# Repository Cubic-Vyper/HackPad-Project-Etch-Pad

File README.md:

# HackPad-Project-Etch-Pad
This is my repository for my Hackpad called "Etch-Pad".
This HackPad has two layers. In the first, the rotary encoders control the mouse like an Etch-n-Sketch, and the switchs have some useful macros. On the second layer the rotary encoders control volume and led brightness, and the switches have some useful macros.

Blueprint Page:https://blueprint.hackclub.com/projects/10732

Buttons:
Layer 0: Screenshot, Paste, Parrot, Space

Layer 1: Previous track, Play/Pause+RickRoll, Next track, Spam E

Encoders:
Layer 0: Mouse control

Layer 1: Volume control + Led brightness

Parts Used:

Seeed XIAO RP2040

4x MX-Style switches

2x EC11 Rotary encoders

4x white blank DSA keycaps

4x SK6812 MINI-E LEDs

4x M3x16mm screws

4x M3x5mx4mm heatset inserts

____________________________________________________________________________________________________

This is the assembled model of my hackpad and what it should look like:

Schematic Screenshot:

PCB Screenshot:

to assemble the case, first collect all of your parts:

next insert the assembled PCB into the bottem half of the case:

then place the top plate on and screw it together:

finnaly attach the keycaps and the enchoder knobs:

plug it up:

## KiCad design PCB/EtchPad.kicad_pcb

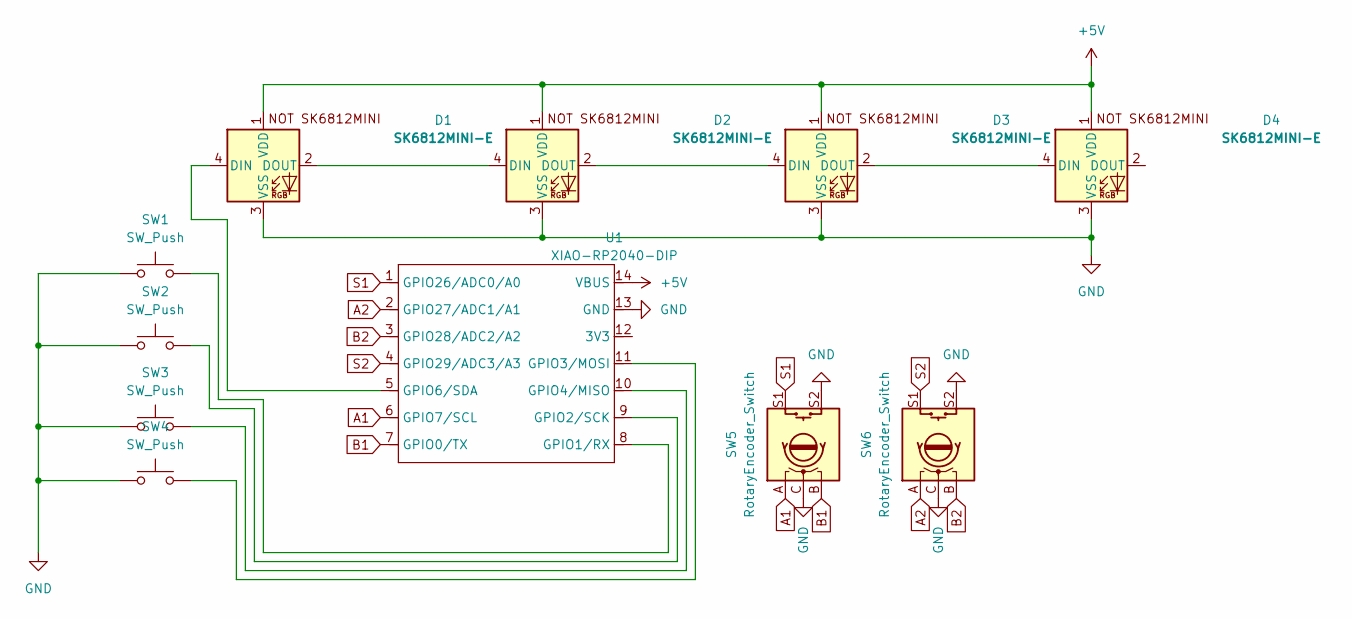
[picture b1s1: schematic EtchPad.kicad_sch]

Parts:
D1, D2, D3, D4: SK6812MINI-E; SK6812MINI-E_fixed
SW1, SW2, SW3, SW4: SW_Push; SW_Cherry_MX_1.00u_PCB
SW5, SW6: RotaryEncoder_Switch; RotaryEncoder_Alps_EC11E-Switch_Vertical_H20mm
U1: XIAO-RP2040-DIP

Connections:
+5V: D1.1 (VDD), D2.1 (VDD), D3.1 (VDD), D4.1 (VDD), U1.14 (VBUS)
A1: SW5.A, U1.6 (GPIO7/SCL)
A2: SW6.A, U1.2 (GPIO27/ADC1/A1)
B1: SW5.B, U1.7 (GPIO0/TX)
B2: SW6.B, U1.3 (GPIO28/ADC2/A2)
GND: D1.3 (VSS), D2.3 (VSS), D3.3 (VSS), D4.3 (VSS), SW1.1, SW2.1, SW3.1, SW4.1, SW5.C, SW5.S2, SW6.C, SW6.S2, U1.13 (GND)
unnamed: D1.4 (DIN), U1.5 (GPIO6/SDA)
unnamed: D1.2 (DOUT), D2.4 (DIN)
unnamed: D2.2 (DOUT), D3.4 (DIN)
unnamed: D3.2 (DOUT), D4.4 (DIN)
unnamed: SW1.2, U1.8 (GPIO1/RX)
unnamed: SW2.2, U1.9 (GPIO2/SCK)
unnamed: SW4.2, U1.11 (GPIO3/MOSI)
unnamed: SW3.2, U1.10 (GPIO4/MISO)
S1: SW5.S1, U1.1 (GPIO26/ADC0/A0)
S2: SW6.S1, U1.4 (GPIO29/ADC3/A3)

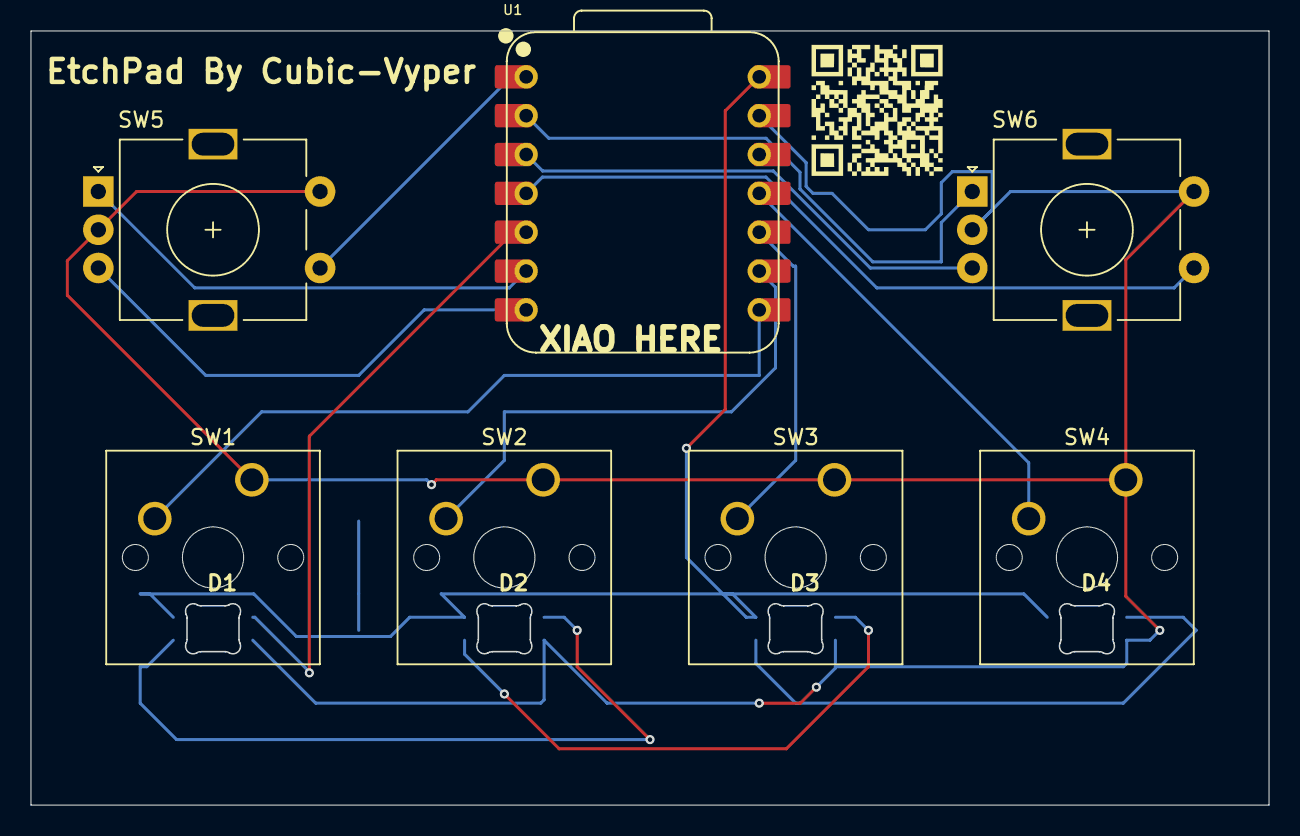
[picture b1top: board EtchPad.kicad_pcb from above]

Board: 2 copper layers, 80.9 x 50.6 mm, 11 parts (0 on the bottom side), 16 nets.

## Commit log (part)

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2026-02-06 Create delete
2026-02-06 Create 1
